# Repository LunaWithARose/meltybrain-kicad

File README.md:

# MeltyBrain PCB
### Custom printed circuit board for a Melty Brain Combat Robot

## Overview

This project involves the design and development of a custom PCB for a Melty Brain combat robot.

A Melty Brain robot uses rotational motion to achieve directional movement and control. Unlike conventional robots, which rely on a fixed forward-facing orientation, a Melty Brain robot must account for its continuously changing orientation while spinning.

The goal of this project is to develop a compact electronics platform tailored to the requirements of a Melty Brain robot.

The PCB is designed around a **34 × 34 mm form factor**, with an emphasis on compact component placement, electrical reliability, and integration into the robot.

## Design Goals

- Develop a custom PCB tailored to the Melty Brain robot architecture.
- Maintain a compact 34 × 34 mm footprint.
- Consider electrical protection and power distribution.
- Design a board that can be integrated into a space-constrained combat robot.

## PCB Design

The board layout is being developed with consideration for component placement, routing, board dimensions, and electrical requirements.

### PCB Layout

*Top-side PCB layout showing component placement and routing.*

*Back-side PCB layout showing component placement and routing.*

*Three-dimensional rendering of the PCB.*

## Repository Structure
```
MeltyBrain-PCB/
│
├── README.md
│
├── images/
│       ├── melty-front.png
│       ├── melty-back.png
│       ├── melty-3d-front.png
│       └── melty-3d-back.png
│
├── hardware/
    ├── schematics
    └── pcbs
```

Directory structure is a suggested organization; adjust it to match the actual repository contents.

## Engineering Considerations

Several considerations are important throughout the design process:

- **Power distribution:** Ensuring that the board's power architecture accommodates the electrical demands of the robot.
- **Cost** Balancing component choice and demands with cost.
- **PCB layout:** Balancing component placement, routing, and board size.
- **Mechanical integration:** Ensuring the PCB fits within the robot's available space.
- **Reliability:** Designing with the operating environment and electrical stresses of a combat robot in mind.

## Development Progress

- [x] Initial PCB design
- [x] Component placement and layout development
- [x] Complete PCB routing
- [x] Design rule check (DRC)
- [x] Final schematic and layout review
- [ ] PCB fabrication
- [ ] Component assembly
- [ ] Electrical validation and testing
- [ ] Integration into robot

*Progress checklist reflects the current development stage and will be updated as the project advances.*

## Future Work

Future development will focus on preparing manufacturing files and validating the assembled board.

## Author

Designed and developed by **Luna Waller**.

Electrical Engineering Student | Washington State University

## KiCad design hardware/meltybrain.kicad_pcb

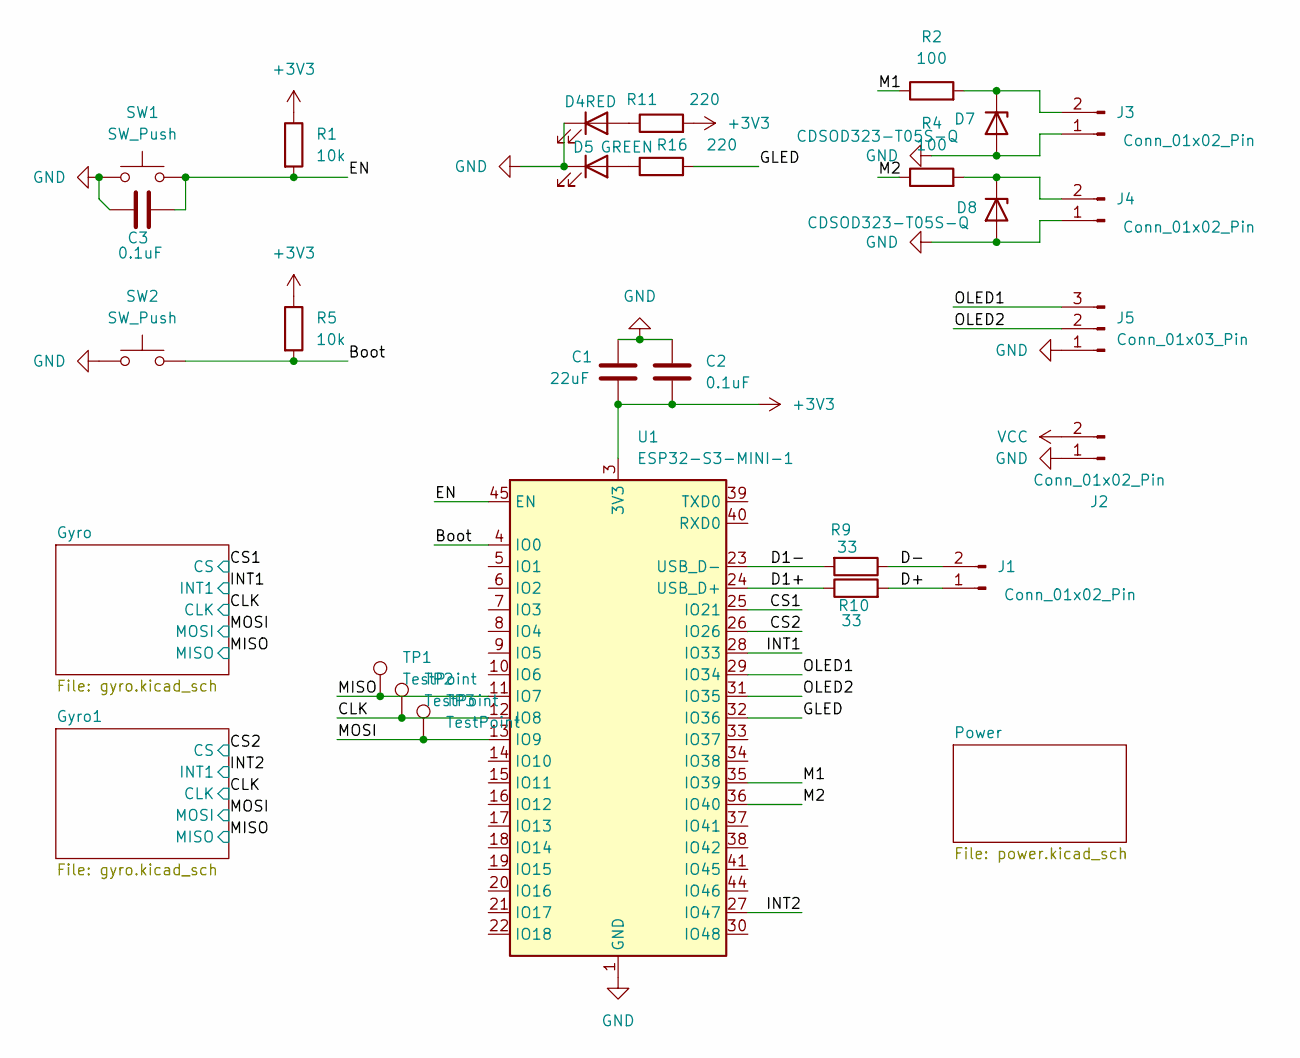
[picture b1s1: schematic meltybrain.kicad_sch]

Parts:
C1: 22uF; C_0805_2012Metric
C2, C3: 0.1uF; C_0603_1608Metric
D4: RED; LED_0603_1608Metric
D5: GREEN; LED_0603_1608Metric
D7, D8: CDSOD323-T05S-Q; D_SOD-323
J1, J2, J3, J4: Conn_01x02_Pin; JST_GH_BM02B-GHS-TBT_1x02-1MP_P1.25mm_Vertical
J5: Conn_01x03_Pin; JST_GH_BM03B-GHS-TBT_1x03-1MP_P1.25mm_Vertical
R1, R5: 10k; R_0603_1608Metric
R2, R4: 100; R_0603_1608Metric
R9, R10: 33; R_0603_1608Metric
R11, R16: 220; R_0603_1608Metric
SW1, SW2: SW_Push; PinHeader_1x02_P2.00mm_Vertical
TP1, TP2, TP3: TestPoint; TestPoint_Pad_D1.0mm
U1: ESP32-S3-MINI-1; ESP32-S2-MINI-1

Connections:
+3V3: C1.2, C2.2, R1.1, R5.1, R11.2, U1.3 (3V3); also elsewhere on the board
/Boot: R5.2, SW2.2, U1.4 (IO0)
/CLK: TP2.1 (1_1), U1.12 (IO8); also elsewhere on the board
/CS1: U1.25 (IO21); also elsewhere on the board
/CS2: U1.26 (IO26); also elsewhere on the board
/D1+: R10.1, U1.24 (USB_D+)
/D1-: R9.2, U1.23 (USB_D-)
/D+: J1.1, R10.2
/D-: J1.2, R9.1
/EN: C3.2, R1.2, SW1.2, U1.45 (EN)
/GLED: R16.2, U1.32 (IO36)
/INT1: U1.28 (IO33); also elsewhere on the board
/INT2: U1.27 (IO47); also elsewhere on the board
/M1: R2.1, U1.35 (IO39)
/M2: R4.1, U1.36 (IO40)
/MISO: TP1.1 (1_1), U1.11 (IO7); also elsewhere on the board
/MOSI: TP3.1 (1_1), U1.13 (IO9); also elsewhere on the board
/OLED1: J5.3, U1.29 (IO34)
/OLED2: J5.2, U1.31 (IO35)
GND: C1.1, C2.1, C3.1, D4.1 (K), D5.1 (K), D7.2 (A), D8.2 (A), J2.1, J3.1, J4.1, J5.1, SW1.1, SW2.1, U1.1 (GND), U1.2 (GND), U1.42 (GND), U1.43 (GND), U1.46 (GND), U1.47 (GND), U1.48 (GND), U1.49 (GND), U1.50 (GND), U1.51 (GND), U1.52 (GND), U1.53 (GND), U1.54 (GND), U1.55 (GND), U1.56 (GND), U1.57 (GND), U1.58 (GND), U1.59 (GND), U1.60 (GND), U1.61 (GND), U1.62 (GND), U1.63 (GND), U1.64 (GND), U1.65 (GND); also elsewhere on the board
unnamed: D4.2 (A), R11.1
unnamed: D5.2 (A), R16.1
unnamed: D7.1 (K), J3.2, R2.2
unnamed: D8.1 (K), J4.2, R4.2
VCC: J2.2; also elsewhere on the board

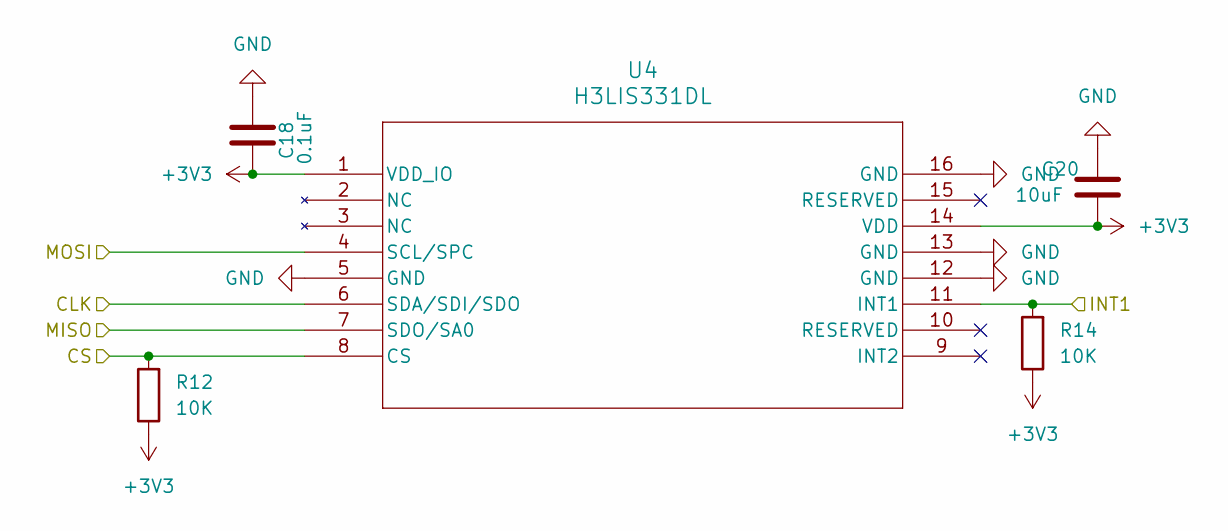
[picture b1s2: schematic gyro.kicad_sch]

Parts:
C18: 0.1uF; C_0603_1608Metric
C20: 10uF; C_0805_2012Metric
R12, R14: 10K; R_0603_1608Metric
U4: H3LIS331DL; TFLGA16_3X3X1_STM

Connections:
+3V3: C18.1, C20.2, R12.1, R14.1, U4.1 (VDD_IO), U4.14 (VDD); also elsewhere on the board
/CLK: U4.6 (SDA/SDI/SDO); also elsewhere on the board
/CS1: R12.2, U4.8 (CS); also elsewhere on the board
/INT1: R14.2, U4.11 (INT1); also elsewhere on the board
/MISO: U4.7 (SDO/SA0); also elsewhere on the board
/MOSI: U4.4 (SCL/SPC); also elsewhere on the board
GND: C18.2, C20.1, U4.5 (GND), U4.12 (GND), U4.13 (GND), U4.16 (GND); also elsewhere on the board

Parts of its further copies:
C19: 0.1uF; C_0603_1608Metric
C21: 10uF; C_0805_2012Metric
R13, R15: 10K; R_0603_1608Metric
U5: H3LIS331DL; TFLGA16_3X3X1_STM

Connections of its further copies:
+3V3: C19.1, C21.2, R13.1, R15.1, U5.1 (VDD_IO), U5.14 (VDD); also elsewhere on the board
/CLK: U5.6 (SDA/SDI/SDO); also elsewhere on the board
/CS2: R13.2, U5.8 (CS); also elsewhere on the board
/INT2: R15.2, U5.11 (INT1); also elsewhere on the board
/MISO: U5.7 (SDO/SA0); also elsewhere on the board
/MOSI: U5.4 (SCL/SPC); also elsewhere on the board
GND: C19.2, C21.1, U5.5 (GND), U5.12 (GND), U5.13 (GND), U5.16 (GND); also elsewhere on the board

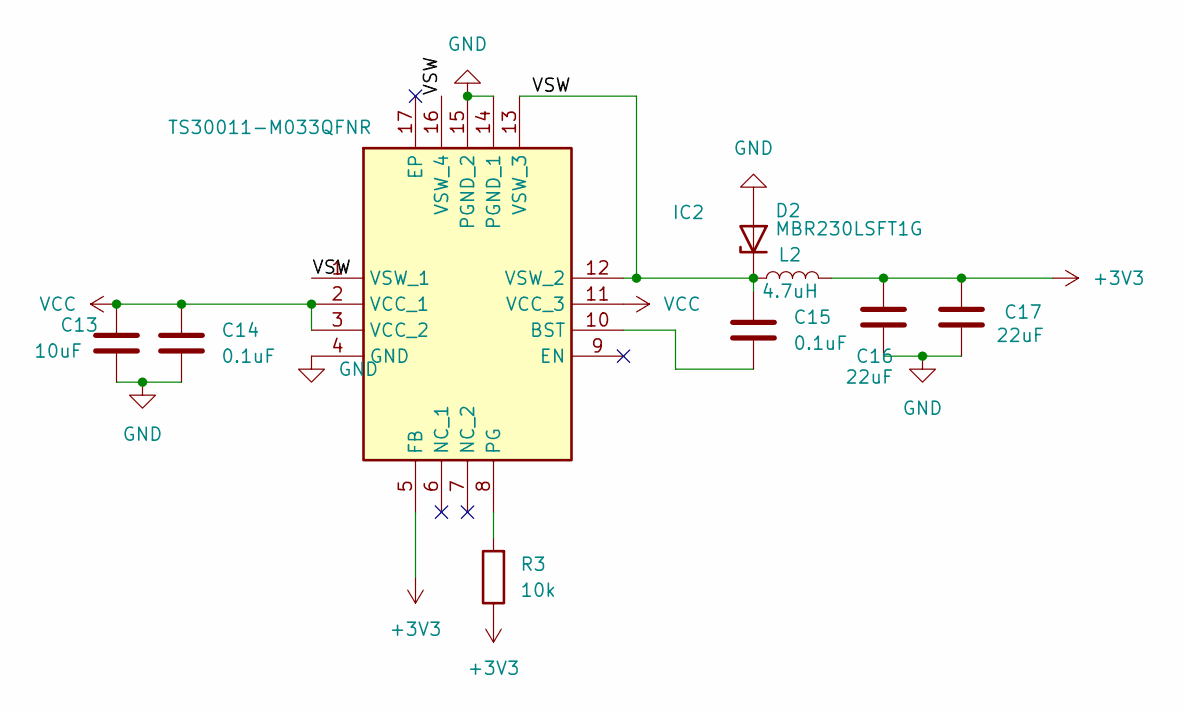
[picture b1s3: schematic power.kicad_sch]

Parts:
C13: 10uF; C_0805_2012Metric
C14, C15: 0.1uF; C_0603_1608Metric
C16, C17: 22uF; C_0805_2012Metric
D2: MBR230LSFT1G; D_SOD-123F
IC2: TS30011-M033QFNR; QFN50P300X300X100-17N-D; Mouser Part Number 947-TS30011-M033QFNR
L2: 4.7uH; L_1206_3216Metric
R3: 10k; R_0603_1608Metric

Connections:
+3V3: C16.1, C17.1, IC2.5 (FB), L2.2, R3.1; also elsewhere on the board
/Power/VSW: C15.1, D2.1 (K), IC2.1 (VSW_1), IC2.12 (VSW_2), IC2.13 (VSW_3), IC2.16 (VSW_4), L2.1
GND: C13.2, C14.2, C16.2, C17.2, D2.2 (A), IC2.4 (GND), IC2.14 (PGND_1), IC2.15 (PGND_2); also elsewhere on the board
unnamed: C15.2, IC2.10 (BST)
unnamed: IC2.8 (PG), R3.2
VCC: C13.1, C14.1, IC2.2 (VCC_1), IC2.3 (VCC_2), IC2.11 (VCC_3); also elsewhere on the board

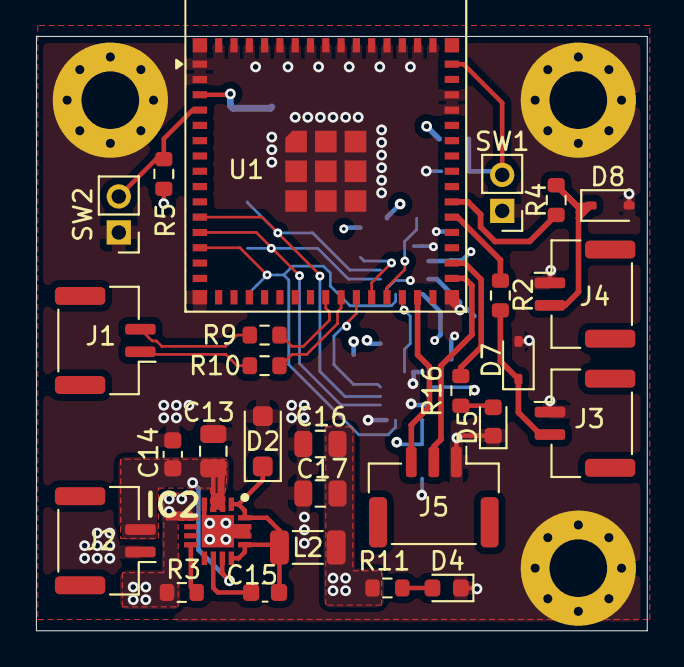
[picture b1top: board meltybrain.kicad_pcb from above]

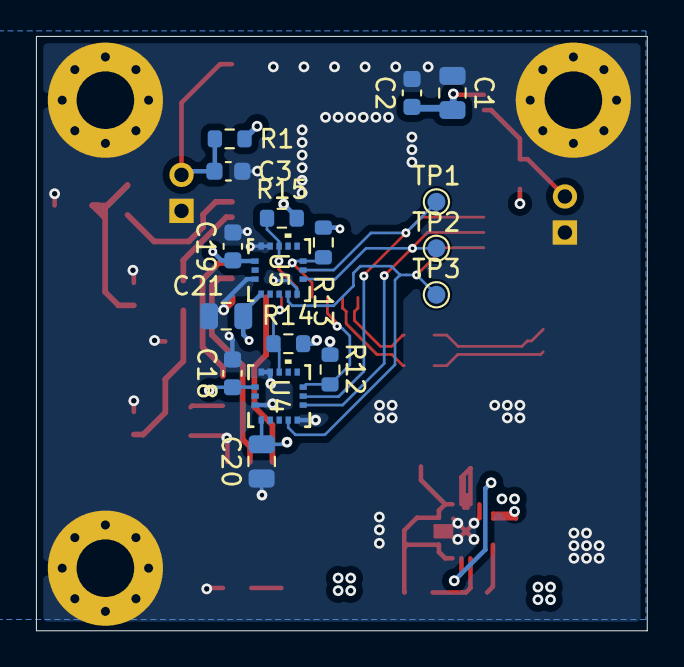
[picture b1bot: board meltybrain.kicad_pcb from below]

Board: 4 copper layers, 33.9 x 33.0 mm, 45 parts (17 on the bottom side), 28 nets.
